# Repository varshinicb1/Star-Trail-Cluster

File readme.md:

# Star Trail Instrument Cluster

A premium digital instrument cluster for the **CrowPanel 1.28" Round ESP32-S3 Display** — a complete automotive HUD replacement with a companion mobile app.

## Screenshots

### Firmware — LVGL PC simulator (`simulator/`)
Rendered from the actual firmware widget code (not mockups) — see [`BenzCluster/docs/widgets/`](BenzCluster/docs/widgets/) and the [firmware README](BenzCluster/README.md#widget-preview) for the full breakdown.

### Companion app — Android emulator (`star_trail_emu`)
Captured live on a real Android emulator, not simulated screenshots — every screen shown is the actual installed release build (v2.0.2) running end to end, including a live call to the public GitHub API on the Updates screen.

| Screen | Description |
|--------|-------------|
| [Welcome](docs/screenshots/01_welcome.png) | Theme picker (Star Trail chrome / Illuminati) + entry point |
| [Dashboard](docs/screenshots/04_dashboard.png) | Live telemetry — linear compass matching the firmware widget exactly, alt/temp/pressure, G-force |
| [Widget Designer](docs/screenshots/06_designer.png) | Drag-and-drop custom widget layout editor, pushes straight to the device |
| [Controls](docs/screenshots/07_controls.png) | Device configuration menu |
| [Attitude Style](docs/screenshots/08_attitude_style.png) | Pick the attitude-indicator face shown on the gadget, like a watch face |
| [Factory Calibration](docs/screenshots/09_factory_cal.png) | One-time installer wizard — orientation zero + magnetometer figure-8 |
| [LED Settings](docs/screenshots/11_led_settings.png) | Color, brightness, and pattern control for the 5 NeoPixels |
| [System Settings](docs/screenshots/12_system_settings.png) | Display brightness, screen timeout, WiFi, device diagnostics |
| [Updates (OTA)](docs/screenshots/13_ota.png) | One-tap firmware update straight from a GitHub release, plus app auto-update |
| [Settings](docs/screenshots/14_config.png) | Connection (BLE/WiFi/Simulator), theme, and app info |

```
ESP32-S3 (BenzCluster firmware)    ◄── BLE/WiFi ──►    Flutter App (star_trail)
├── 7 LVGL widgets on 240x240 GC9A01              ├── Real-time dashboard mirror
├── MPU9250 9-DOF + BME280 sensors                ├── Widget/LED/System controls
├── 5x NeoPixel status LEDs                       ├── OTA firmware updates
├── BLE HID media keys                            └── BLE scan + WiFi connect
├── BLE phone notifications
├── WiFi web dashboard + REST API
└── Rotary encoder navigation
```

## Features

### Hardware
- **Display:** 1.28" round GC9A01 (240x240) SPI display
- **Sensors:** MPU6050 (accelerometer + gyroscope), QMC5883L (magnetometer), BME280 (temperature, pressure, altitude)
- **Input:** Rotary encoder with push button, capacitive touch (CST816D)
- **Lighting:** 5 individually addressable NeoPixel LEDs
- **Connectivity:** WiFi (ESP32-S3), BLE (NimBLE stack)

### Firmware (BenzCluster)
- 8 swipeable LVGL widgets: **Clock, Compass, Attitude Indicator, Altitude/Temperature, G-Force, Music Remote, Airplane, Custom**
- Linear scrolling compass with true-north heading (tilt-compensated, hard/soft-iron corrected)
- 4 selectable attitude-indicator styles (Classic ICAO, Fullscreen, Minimal, Tape/EFIS), switchable from the app like a watch face
- One-time factory calibration (mount-tilt orientation zero + magnetometer figure-8) — end customers never calibrate
- Custom widget designer: user-designed layouts pushed from the app render live on-device
- BLE HID media control (play/pause/next/prev/volume)
- WiFi web dashboard with REST API on port 80
- OTA firmware updates over WiFi (pushed automatically from the app, or manual .bin upload)
- Rotary encoder for brightness, volume, widget navigation
- 3-second encoder hold for system overlay (sensor viewer, system info, calibration)

### Companion App (star_trail)
- Real-time dashboard mirror — widgets match the firmware exactly (same linear compass, same colours)
- 2 themes: **Star Trail** (premium black/gunmetal/chrome, real Mercedes emblem, default), **Illuminati** (VW red)
- Drag-and-drop widget designer that pushes custom layouts straight to the device
- Attitude style picker and factory calibration wizard
- Widget configuration (enable/disable, reorder, swipe direction, knob mode)
- LED control (color picker, patterns, brightness, speed)
- System settings (display brightness, screen timeout, WiFi config, device info)
- One-tap firmware update straight from a GitHub release (manual .bin upload kept as a fallback)
- App auto-update via GitHub Releases (checks for new APK versions, downloads & installs)
- Connection via BLE scan, WiFi IP, or built-in simulator mode

## Quick Start

### Prerequisites
- CrowPanel 1.28" ESP32-S3 Round Display
- Arduino IDE (with ESP32-S3 board support) or PlatformIO
- Flutter SDK 3.12.2+ (for companion app)
- USB-C cable

### Flash Firmware (Arduino IDE)
1. Open `BenzCluster/BenzCluster.ino` in Arduino IDE
2. Install required libraries:
   - Adafruit NeoPixel 1.15.3+
   - ArduinoJson 7.4.2+
   - LovyanGFX 1.2.19+
   - lvgl 8.3.11
   - NimBLE-Arduino 2.3.7+
   - ESPAsyncWebServer 3.1.0+
3. Board: **ESP32-S3 Dev Module**
4. Partition Scheme: **Huge APP (3MB No OTA/1MB SPIFFS)** (or use `partitions.csv` for dual OTA)
5. Select the correct COM port
6. Click **Upload**

### Build Companion App
```bash
cd flutter_app/

# Analyze for errors
flutter analyze

# Debug APK
flutter build apk --debug

# Release APK
flutter build apk --release

# Or run on connected device
flutter run
```

The release APK will be at `flutter_app/build/app/outputs/flutter-apk/app-release.apk`.

### OTA Update (from CLI)
```bash
python BenzCluster/ota_upload.py --ip 192.168.x.x --bin build/BenzCluster.ino.bin
```

## Architecture

### Communication
The ESP32-S3 runs a WiFi access point (or connects to your network) with a REST API server on port 80, and simultaneously acts as a BLE peripheral broadcasting sensor data and accepting commands. The Flutter app connects via either channel.

### REST API Endpoints
| Endpoint | Method | Params | Description |
|----------|--------|--------|-------------|
| `/api/status` | GET | — | Full sensor + system JSON |
| `/api/led` | GET | `state`, `color`, `brightness`, `pattern`, `speed` | LED control |
| `/api/brightness` | GET | `v` | Display brightness |
| `/api/timeout` | GET | `v` | Screen timeout seconds |
| `/api/music` | GET | `cmd` | Media commands (play/next/prev/vol_up/vol_down) |
| `/api/widgets` | GET | `enabled`, `order`, `swipe`, `knob` | Widget configuration |
| `/api/app-version` | GET | — | Returns Flutter app version info for auto-update |
| `/reboot` | GET | — | Reboot device |
| `/update` | POST | firmware.bin | OTA firmware update |

### BLE Protocol
- **Notify characteristic:** Broadcasts JSON with `heading`, `pitch`, `roll`, `temp`, `alt_ft`, `pressure`, accelerometer/magnetometer raw data, uptime, heap, RSSI, IP, SSID
- **Write characteristic:** Accepts commands matching the REST API path format

### Widget System
The firmware renders 7 widgets swipeable on the round display. Each widget is a separate LVGL screen created in its own `.cpp`/`.h` file pair. The companion app mirrors these with `CustomPainter` implementations.

## Hardware Pinout

| Component | Interface | Pins |
|-----------|-----------|------|
| GC9A01 Display | SPI | SCLK=10, MOSI=11, DC=3, CS=9, RST=14, BL=46 |
| CST816D Touch | I2C (Wire1) | SDA=6, SCL=7, RST=13, INT=5 |
| MPU9250 | I2C (Wire) | SDA=38, SCL=39, ADDR=0x68 |
| QMC5883L | I2C (Wire) | ADDR=0x0D |
| BME280 | I2C (Wire) | ADDR=0x76 |
| Rotary Encoder | GPIO | A=45, B=42, SW=41 |
| NeoPixel | GPIO | PIN=48, COUNT=5 |

## Project Structure

```
CrowPanel_Repo/
├── BenzCluster/          ESP32-S3 firmware (Arduino sketch)
├── flutter_app/          Flutter companion app (star_trail)
├── Datasheet/            Component datasheets
├── Eagle_SCH&PCB/        Circuit schematic and PCB layout
├── 3D file/              Enclosure STEP model
├── simulator/            PC LVGL simulator
├── factory_firmware/     Pre-compiled factory binaries + flash tool
├── factory_soucecode/    Factory SquareLine Studio project
├── example/              Example sketches and third-party libraries
└── SensorDiag/           Standalone sensor diagnostic tool
```

## CI/CD & Release

### Building for Release

**Firmware**
```bash
arduino-cli compile --fqbn esp32:esp32:esp32s3 --partitions-scheme huge_app BenzCluster/
```

**Flutter APK**
```bash
cd flutter_app/
flutter build apk --release --build-name=2.0.2 --build-number=5
```

Release APK: `flutter_app/build/app/outputs/flutter-apk/app-release.apk` (~54.7MB)
Debug APK: `flutter_app/build/app/outputs/flutter-apk/app-debug.apk`

### Creating a GitHub Release
1. Build firmware and APK (commands above)
2. Create a GitHub Release with tag `vX.Y.Z` (match `--build-name`), **repo must be public** — GitHub's REST API returns 404 for unauthenticated release lookups on private repos, which silently breaks both the app and firmware auto-update
3. Upload `app-release.apk` AND the firmware `.bin` as release assets — the app derives both the app update and the firmware update from the same release
4. `githubRepo` in `lib/services/update_service.dart` already points at this repo
5. Users' apps auto-detect the new app version on next launch; the Updates screen offers one-tap firmware push whenever a new `.bin` is published

### Auto-Update Flow
- `UpdateService` checks the GitHub Releases API once per launch, deriving both app-APK and firmware-.bin info from the same release
- Compares versions semantically against the installed app version
- App: downloads the APK to temp storage and opens it via Android FileProvider (requires Android 7+)
- Firmware: downloads the `.bin` into memory and pushes it to the device over WiFi automatically (`POST /update`) — no manual file picking required; manual upload remains as a fallback

### Verification
- `flutter analyze` — 0 issues
- `flutter test` — 23 tests pass
- Firmware: compiles to ~2.03MB (64% of the 3MB app partition)
- Verified live: LVGL PC simulator (all 10 widget screens) + a real Android emulator (all app screens, including a live GitHub API round-trip on the Updates screen) — see Screenshots above

## License

Private project. All rights reserved.

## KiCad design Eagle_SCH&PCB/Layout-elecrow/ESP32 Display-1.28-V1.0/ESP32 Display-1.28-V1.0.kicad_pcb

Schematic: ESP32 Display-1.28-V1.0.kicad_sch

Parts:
ANT0: BT_ANT
BOOT0: BOOT; SW-4.5_4.5
C1: 1UF; 0402
C2, C4: NC; C0402
C3, C5, C26: 1uF; C0402
C6, C11, C15, C16, C19: 100NF; 0603
C7: 1uF; C0603
C8: 10NF; C0603
C9, C13: 12pF; 0402
C10, C12, C17, C18, C20, C36: 22uF; 0805
C14: 100NF; C0603
C118: NC/3PF; 0603
J3: EC3501-C15H30P3
J34, J36, J37: 1.25-4P-SMT-A; 1.25-4P立贴
K112: BUTTON_2P
L2: 100M-600R; L0603
L3: 2.2UH; L0420
LCD0: LCD-1.28-16P-1.28; 0.5MM-16P
P1, P2, P3, P4, P5, P6, P7, P8, P9, P10, P11, P12, P13, P14, P15, P16, P17, P18, P19, P20: PADPAD-1.0MM; PAD-1.0MM
PWR0: Green; LED-0603
Q1, Q7, Q11: S9013; SOT23@1
Q2, Q5, Q6, Q8, Q9: BSN20; SOT23
Q3, Q4, Q10: PMOS-3401-4A; SOT-23
R1, R4, R7, R8, R13, R14, R15, R16, R19, R20, R21, R22, R23, R27, R29, R30, R50: 10K; 0402
R2: 10R; R0603
R3: NC; 0402
R5, R9, R11, R12, R35, R36, R38, R39: 10k; 0402
R6: 0R; 0402
R10: 1K; 0402
R28: 4.7K; 0402
R31: 24K; 0402
R33: 100K; 0402
R37: 100R; 0402
R40: 110K; 0402
R43, R44: 10R; R0402
RESET0: RESET; SW-4.5_4.5
RGB1, RGB2, RGB3, RGB4, RGB5: RGB4020_E; RGB4020
T1, T2: T2.5-A; T-2.5
U1: ESP-S3-QFN56(7×7MM)
U2: RY3420; SOT23-5
U7: AIP74LVC1T45GB236; SOT23-6L
U$17: FLASHSOP8_W25X20CL; FLASHSOP8_SOP8
U$27: CON-12P-0.5-U; CON-0.5-12P-U
U$28, U$30, U$31: T-2-1.1
Y1: 3225_40M; CRYSTAL-3.2-2.5

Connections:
/3.3V: C26.1, C118.2, L2.2, U1.2 (VDD3P3), U1.3 (VDD3P3@), U1.20 (VDD3P3_RTC)
/ESP_RXD: Q9.2 (S), R38.P$1 (1), U1.50 (U0RXD)
/ESP_TXD: Q8.2 (S), R39.P$2 (2), U1.49 (U0TXD)
/GPIO0: BOOT0.P$2, BOOT0.P$3, U1.5 (GPIO0)
/GPIO1: R22.P$2 (2), U1.6 (GP1O1)
/GPIO2: R23.P$2 (2), U1.7 (GP1O2)
/GPIO4: P12.P$1, U1.9 (GP1O4), U$27.P$3 (3)
/GPIO12: P13.P$1, U1.17 (GP1O12), U$27.P$4 (4)
/GPIO38-SDA: Q5.2 (S), R36.P$2 (2), U1.43 (GP1O38)
/GPIO38-SDA-: J36.2, P17.P$1, Q5.3 (D), R11.P$1 (1), U$27.P$8 (8)
/GPIO39-SCL: Q6.2 (S), R35.P$1 (1), U1.44 (GP1O39)
/GPIO39-SCL-: J36.1, P16.P$1, Q6.3 (D), R12.P$1 (1), U$27.P$7 (7)
/GPIO40: PWR0.-, U1.45 (GP1O40)
/GPIO41: K112.P$2, P18.P$1, R21.P$1 (1), U1.47 (GP1O41)
/GPIO42: J3.3 (B), R19.P$1 (1), U1.48 (GP1O42)
/GPIO45: J3.1 (A), R20.P$1 (1), U1.51 (GPIO45)
/GPIO46_BL: R30.P$1 (1), U1.52 (GPIO46)
/GPIO47: U1.37 (GP1O47)
/LCD-3.3: C11.1, LCD0.3 (LEDA), LCD0.4 (VDD), P2.P$1, Q10.3 (D), R13.P$1 (1), R14.P$1 (1), R29.P$1 (1)
/LCD-D/C_IO2: LCD0.7 (D\C), P3.P$1, U1.8 (GP1O3)
/LCD_CLK: LCD0.9 (SCL), P5.P$1, U1.15 (GP1O10)
/LCD_CS: LCD0.8 (CS), P4.P$1, U1.14 (GP1O9)
/LCD_MISO: LCD0.10 (SDA), P6.P$1, U1.16 (GP1O11)
/LCD_RST: LCD0.11 (RESET), P7.P$1, U1.19 (GP1O14)
/LEDK: LCD0.2 (LEDK), P1.P$1, R2.2
/MISO: U1.34 (SPI_MISO), U$17.2 (D0MI)
/OUT_5V: C10.2, J34.3, J36.3, Q4.3 (D)
/RESET: C5.2, R50.P$2 (2), RESET0.P$1, RESET0.P$4, U1.4 (CHIP_PU)
/RGB_DI: R3.P$2 (2), R28.P$1 (1), U1.36 (GP1O48), U7.4 (B)
/SPICS0: U1.32 (SPICS0), U$17.1 (/CS)
/SPIWP: R27.P$2 (2), U1.31 (SPIWP), U$17.3 (/WP)
/TP_INT: LCD0.16 (TP-INT), P11.P$1, U1.10 (GP1O5)
/TP_RST: LCD0.13 (TP-RST), P8.P$1, R13.P$2 (2), U1.18 (GP1O13)
/TP_SCL: LCD0.14 (TP-SCL), P9.P$1, R29.P$2 (2), U1.12 (GP1O7)
/TP_SDA: LCD0.15 (TP-SDA), P10.P$1, R14.P$2 (2), U1.11 (GP1O6)
/UART0_RXD0-: J34.1, P14.P$1, Q9.3 (D), R9.P$1 (1), U$27.P$5 (5)
/UART0_TXD0-: J34.2, P15.P$1, Q8.3 (D), R5.P$1 (1), U$27.P$6 (6)
/USB-D+: J37.3, R44.1, U$27.P$10 (10)
/USB-D-: J37.2, R43.1, U$27.P$9 (9)
/VCC_5V: C15.1, C16.1, C17.2, C18.2, C19.1, C20.2, P20.P$1, Q3.2 (S), Q4.2 (S), R4.P$2 (2), R5.P$2 (2), R9.P$2 (2), R11.P$2 (2), R12.P$2 (2), RGB1.2 (VDD), RGB2.2 (VDD), RGB3.2 (VDD), RGB4.2 (VDD), RGB5.2 (VDD), U2.1 (CE), U2.4 (VIN), U7.1 (VCCA), U$27.P$1 (1), U$27.P$2 (2)
/VDD_3.3V: C3.2, C6.1, C12.2, C14.1, C36.2, L2.1, L3.2, Q5.1 (G), Q6.1 (G), Q8.1 (G), Q9.1 (G), Q10.2 (S), R10.P$2 (2), R19.P$2 (2), R20.P$2 (2), R21.P$2 (2), R28.P$2 (2), R35.P$2 (2), R36.P$1 (1), R38.P$2 (2), R39.P$1 (1), R40.P$2 (2), R50.P$1 (1), U1.46 (VDD3P3_CPU), U1.56 (VDDA@), U7.6 (VCCB)
/VDD_SPI: R27.P$1 (1), U$17.8 (VCC)
/VUSB_IN: J37.1, P19.P$1, Q3.3 (D), R1.P$2 (2)
GND: ANT0.P$1 (GND), BOOT0.P$1, BOOT0.P$4, C1.2, C2.1, C3.1, C4.1, C5.1, C6.2, C7.2, C8.2, C9.2, C10.1, C11.2, C12.1, C13.2, C14.2, C15.2, C16.2, C17.1, C18.1, C19.2, C20.1, C26.2, C36.1, C118.1, J3.2 (C), J3.4 (NC1), J3.5 (NC2), J34.4, J34.5, J34.6, J36.4, J36.5, J36.6, J37.4, J37.5, J37.6, K112.P$1, LCD0.1 (GND), LCD0.5 (GND1), LCD0.6 (GND2), LCD0.12 (GND3), LCD0.17, LCD0.18, Q1.2 (E), Q2.2 (S), Q7.2 (E), Q11.2 (E), R8.P$1 (1), R31.P$1 (1), R33.P$1 (1), RESET0.P$2, RESET0.P$3, RGB1.4 (GND), RGB2.4 (GND), RGB3.4 (GND), RGB4.4 (GND), RGB5.4 (GND), T1.1, T2.1, U1.57 (GND), U2.2 (GND), U7.2 (GND), U7.5 (DIR), U$17.4 (GND), U$27.P$13, U$27.P$14, U$28.P$1, U$31.P$1, Y1.2 (GND@1), Y1.4 (GND@2)
unnamed: ANT0.P$2 (ANT), C2.2, R6.P$1 (1)
unnamed: C7.1, C8.1
unnamed: Q1.1 (B), R1.P$1 (1), R8.P$2 (2)
unnamed: Q1.3 (C), Q3.1 (G), R7.P$1 (1)
unnamed: Q2.3 (D), R2.1
unnamed: Q2.1 (G), R30.P$2 (2), R33.P$2 (2)
unnamed: Q4.1 (G), Q7.3 (C), R16.P$1 (1)
unnamed: Q7.1 (B), R23.P$1 (1)
unnamed: Q10.1 (G), Q11.3 (C), R15.P$1 (1)
unnamed: Q11.1 (B), R22.P$1 (1)
unnamed: R3.P$1 (1), R4.P$1 (1), R37.P$2 (2), U7.3 (A)
unnamed: C4.2, R6.P$2 (2), U1.1 (LNA_IN)
unnamed: PWR0.+, R10.P$1 (1)
unnamed: R31.P$2 (2), R40.P$1 (1), U2.5 (BF)
unnamed: R37.P$1 (1), RGB1.1 (DI)
unnamed: RGB1.3 (DO), RGB2.1 (DI)
unnamed: RGB2.3 (DO), RGB3.1 (DI)
unnamed: RGB3.3 (DO), RGB4.1 (DI)
unnamed: RGB4.3 (DO), RGB5.1 (DI)
unnamed: R43.2, U1.25 (GP1O19/USB_D-)
unnamed: R44.2, U1.26 (GP1O20/USB_D+)
unnamed: C1.1, U1.29 (VDD_SPI)
unnamed: C9.1, U1.54 (XTAL_N), Y1.1 (C1)
unnamed: C13.1, U1.53 (XTAL_P), Y1.3 (C2)
unnamed: L3.1, U2.3 (LX)
unnamed: U1.33 (SPICLK), U$17.6 (CLK)
unnamed: U1.35 (SPI_MOSI), U$17.5 (DIMO)
unnamed: U1.30 (SPIHD), U$17.7 (/HOLD)
unnamed: U$27.P$11 (11), U$27.P$12 (12)

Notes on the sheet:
UART
LCD
KEY
ESP32-S3
LCD+TP
POWER
RGB-LED
I2C
DC-DC
USB
LED

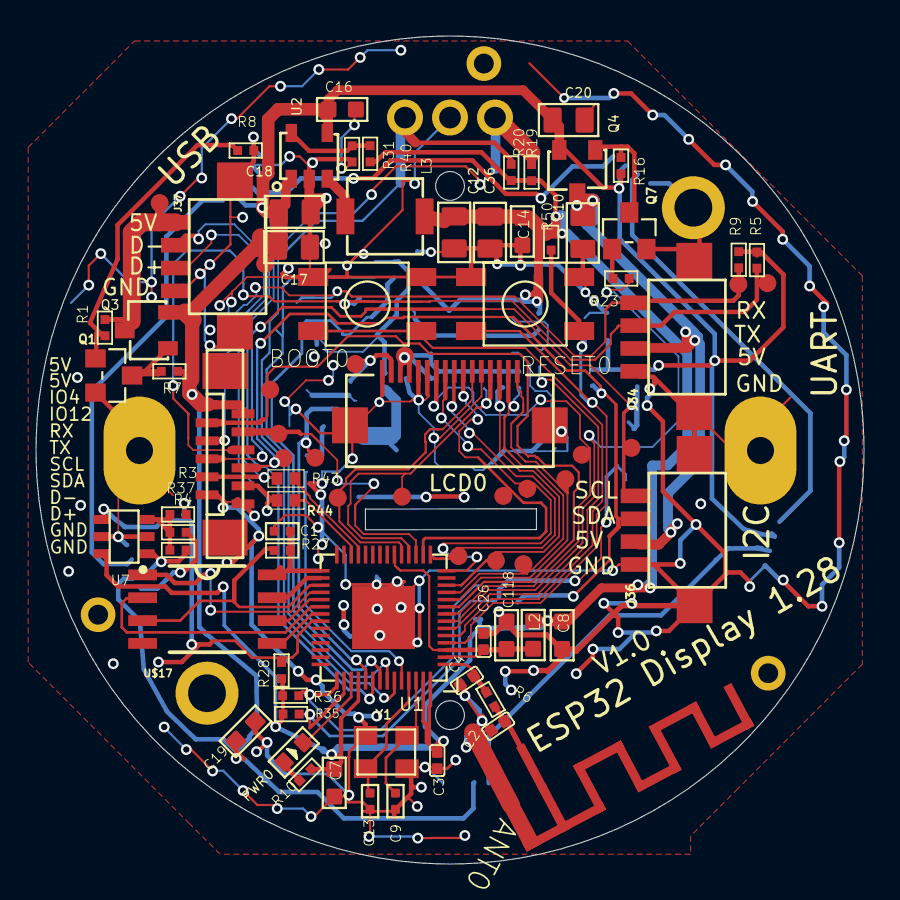
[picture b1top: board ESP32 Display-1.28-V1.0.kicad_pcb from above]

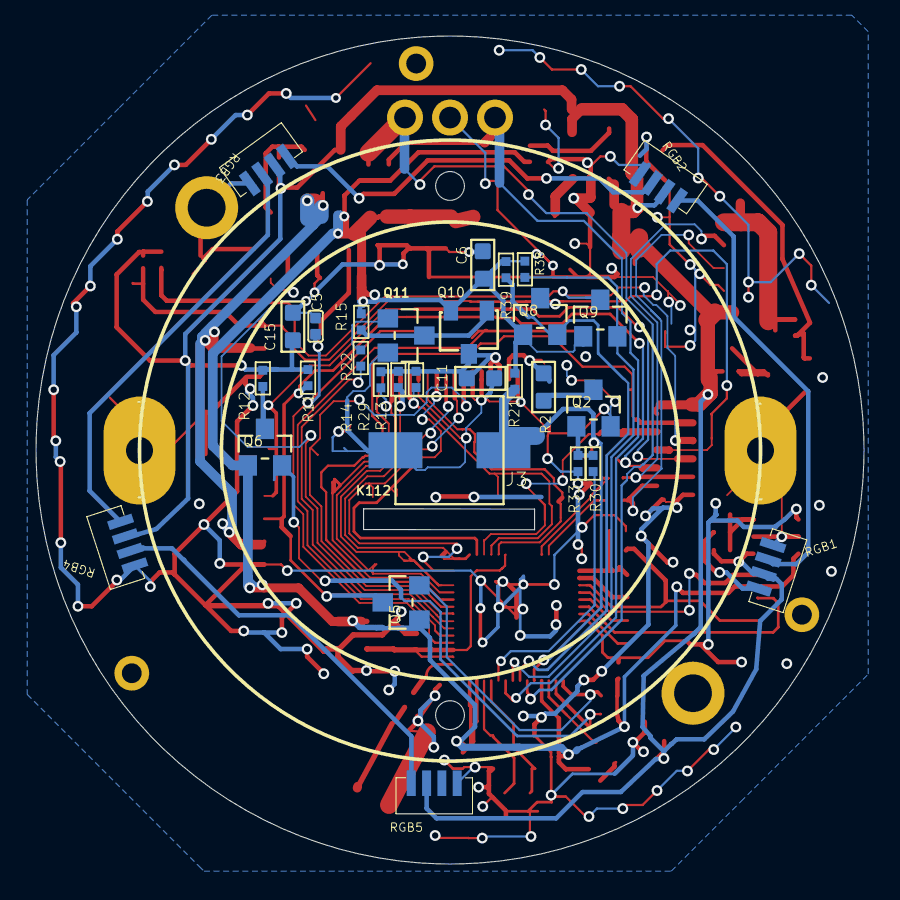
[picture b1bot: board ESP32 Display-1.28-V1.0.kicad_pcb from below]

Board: 2 copper layers, 46.0 x 46.0 mm, 118 parts (33 on the bottom side), 72 nets.

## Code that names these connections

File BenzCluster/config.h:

#ifndef CONFIG_H
#define CONFIG_H

// ============== Hardware Pins ==============
// Display (SPI - GC9A01) - GitMate config
#define TFT_SCLK 10
#define TFT_MOSI 11
#define TFT_DC 3
#define TFT_CS 9
#define TFT_RST 14
#define TFT_BL 46

// Touch (I2C - CST816D on Wire1)
#define TP_SDA 6
#define TP_SCL 7
#define TP_RST 13
#define TP_INT 5

// External Sensors (I2C - Wire)
#define I2C_SDA 38
#define I2C_SCL 39

// Rotary Encoder
#define ENC_A 45
#define ENC_B 42
#define ENC_SW 41

// NeoPixel LEDs
#define LED_PIN 48
#define LED_COUNT 5

// ============== Sensor Addresses ==============
#define MPU9250_ADDR 0x68
#define QMC5883L_ADDR 0x0D // External magnetometer via MPU I2C master
#define BME280_ADDR 0x76

// ============== Location Config ==============
// Bangalore, India
#define MAGNETIC_DECLINATION -1.09f // Bangalore: -1°5' West

// Approximate sea level pressure (hPa) - will be updated via API
#define DEFAULT_SEA_LEVEL_PRESSURE 1013.25f

// Bangalore elevation for reference
#define LOCAL_ELEVATION_METERS 920.0f
#define LOCAL_ELEVATION_FEET 3018.0f

// ============== WiFi Config ==============
// Real credentials live in secrets.h (gitignored, not committed). Copy
// secrets.h.example to secrets.h and fill in your own values.
#include "secrets.h"

#define WEATHER_LAT "12.9716"
#define WEATHER_LON "77.5946"

// NTP Server
#define NTP_SERVER "pool.ntp.org"
#define GMT_OFFSET_SEC 19800 // IST = UTC+5:30
#define DST_OFFSET_SEC 0

// ============== Display Config ==============
#define SCREEN_WIDTH 240
#define SCREEN_HEIGHT 240

// ============== Calibration ==============
#define CALIBRATION_FILE "/calibration/mag.json"
#define PRESSURE_FILE "/calibration/pressure.json"

#endif // CONFIG_H

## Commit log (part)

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2026-02-21 Star Trail v6.0 — Custom Instrument Cluster Firmware
    Features:
    - 7 swipeable widgets: Compass, Attitude, AltTemp, Clock, Music, LED Color, Sensors
    - Hidden System menu (3s encoder hold) with Reboot
    - WiFi OTA updates (ArduinoOTA, hostname: StarTrail)
    - BLE media controller (Star Trail branding, NimBLE HID)
    - Live play/pause icon toggle on encoder click
2026-02-22 Star Trail v7.0: All phases implemented - Magnetometer fix (direct I2C QMC5883L) - GPS, LED widget, welcome screen removed - Full-screen attitude widget (CX=120) - Calibration widget with arc progres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
2026-06-22 Star Trail v9.0: BLE notifications, G-force widget, QMC5883L direct I2C, VW/Illuminati splash themes, expanded OTA dashboard
    Major changes:
    - New BLE notification module (ble_notify) for phone notification mirroring
    - New G-force widget (gforce) for acceleration visualization
    - Removed GPS module (gps.cpp/h) - scope narrowed to instrument cluster
    - Switched magnetometer from internal AK8963 to direct I2C QMC5883L
    - Rewrote attitude indicator (+462 lines) with improved rendering
2026-06-22 Star Trail v10.0: LVGL widget refinements matching code.c visuals, BLE StarTrail data characteristic, Flutter companion app
    - attitude.cpp: Longer wings (55→70px), wider runway (50px line width), sky/gnd rects at 240px circular clip
    - compass.cpp: Bezel resized (outer 234, inner 222), rings pushed outward (ticks 102, dots 98, letters 82, nums 78), larger aircraft (fuselage 90px, wings 45px)
    - alttemp.cpp: 40→100 ticks at 3.6° with major every 10th, added x1000 ft reference window, numbers at radius 72
    - airplane.cpp: Main wings 60→70px, wing tips 20→24px
    - ble_notify.cpp/h: New StarTrail Data Service UUID 00001111-... with READ+NOTIFY, ble_data_notify() function
    - BenzCluster.ino: P
2026-06-22 Star Trail v10.0
2026-06-22 Star Trail v7.0 - original version (BenzCluster only)
2026-06-22 Star Trail v11.0: Premium companion app, 3 themes, full device controls, LVGL PC simulator
    Flutter app rewritten from ground up as consumer-grade companion:
    - 3 themes: StarTrail (Mercedes/cyan), Illuminati (VW/red), DR (purple)
    - Welcome screen with animated logo + 'Welcome DR' + theme picker
    - Premium dashboard: animated compass, G-force dial, data cards, sensor sheet
    - Device controls hub: LED (on/off, 12 colors, 10 patterns), Widget (7 toggles, reorder, swipe/rotary), System (brightness, timeout, WiFi, reboot)
    - Settings: BLE scan/connect, WiFi connect, simulator, theme selector, app info
